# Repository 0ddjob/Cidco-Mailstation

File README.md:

# Cidco MailStation
The MailStation is a Z80 based device from the 20th Century used primarily for email using the POTS (PSTN dial up).<br>

It has a Z80??<br>

W.I.P.Z. ... ?<br>
(Will It Play Zork?)<br>

Apparently [YES!](https://www.fybertech.net/mailstation/images.php)<br>

Unfortunately it seems there is not much active interest or development on the MailStation ... ?<br>

## Videos
- [Cidco MailStation: Part 1 (Quick Look)](https://youtu.be/7wJat_JoTqo)

## [Memory Remapping](/Memory_Remap/)
Thanks to FyberOptic's work detailed [here](https://www.fybertech.net/mailstation/), I have reproduced his schematic and designed this small board to reorganise the memory map of the MailStation so that it might run CP/M.<br>

### Status
10-Jul-2025: Design still a work-in-progress<br>

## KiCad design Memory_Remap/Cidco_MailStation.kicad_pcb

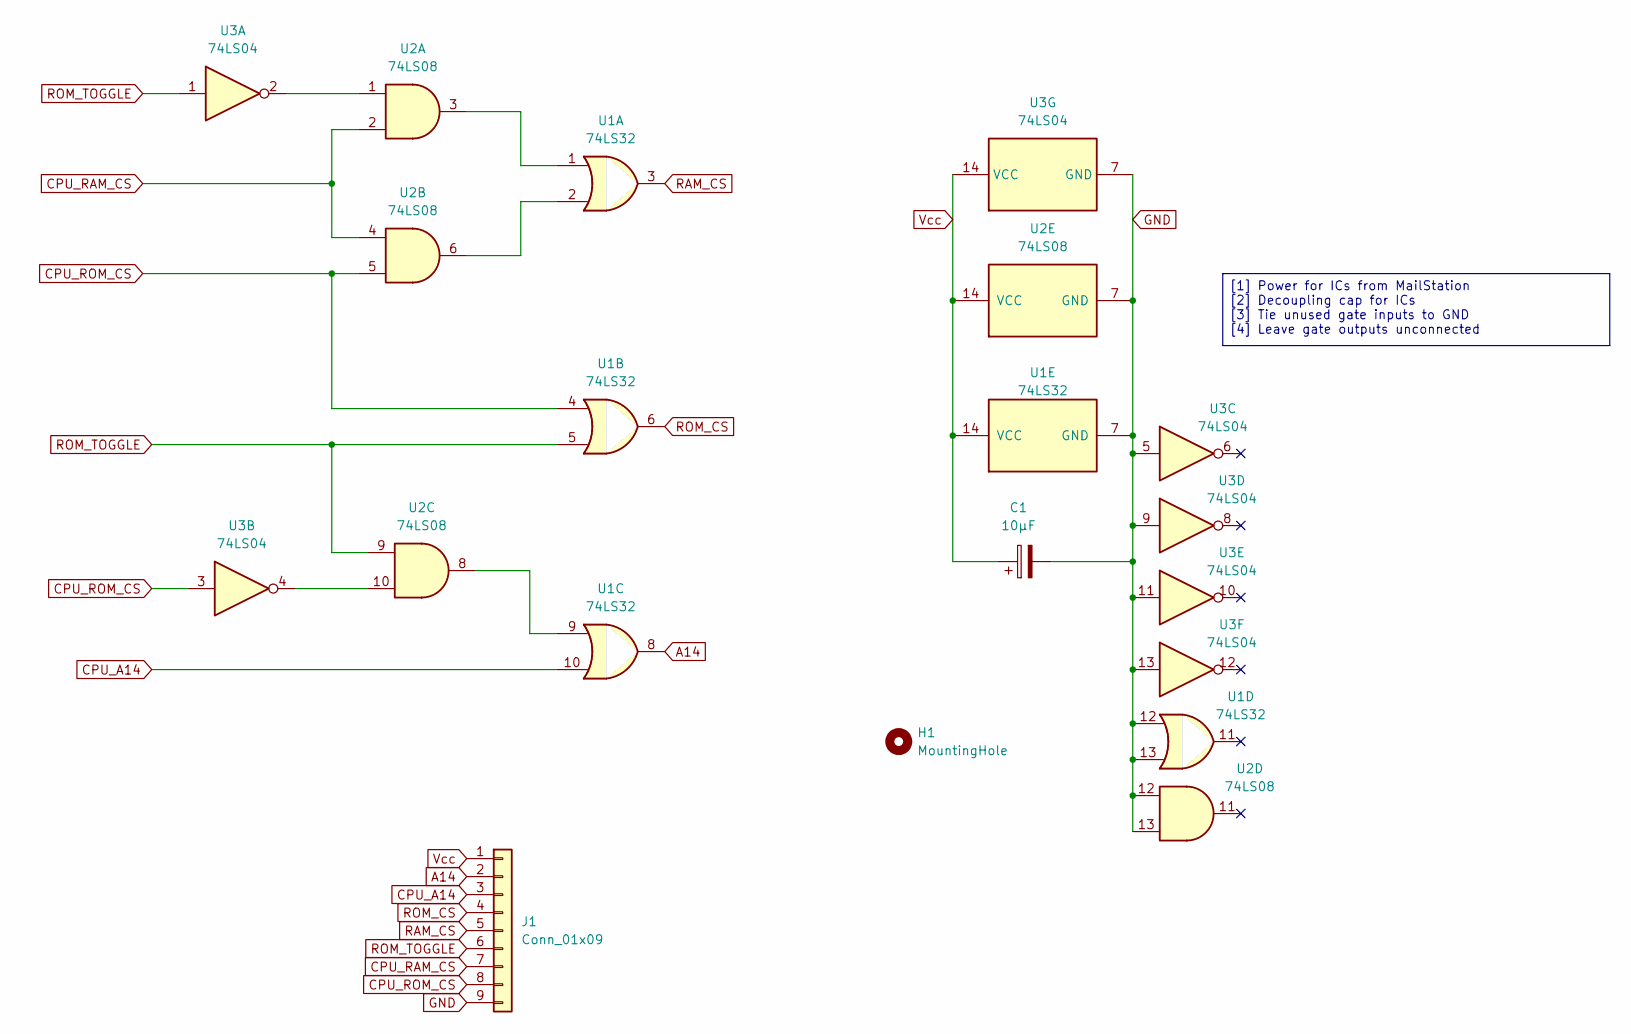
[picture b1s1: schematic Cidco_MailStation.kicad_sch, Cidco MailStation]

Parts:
C1: 10µF; CP_Radial_D5.0mm_P2.50mm
H1: MountingHole; MountingHole_3.2mm_M3
J1: Conn_01x09; PinHeader_1x09_P2.54mm_Vertical
U1: 74LS32; DIP-14_W7.62mm
U2: 74LS08; DIP-14_W7.62mm
U3: 74LS04; DIP-14_W7.62mm

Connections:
A14: J1.2, U1.8
CPU_A14: J1.3, U1.10
CPU_RAM_CS: J1.7, U2.2, U2.4
CPU_ROM_CS: J1.8, U1.4, U2.5, U3.3
GND: C1.2, J1.9, U1.7 (GND), U1.12, U1.13, U2.7 (GND), U2.12, U2.13, U3.5, U3.7 (GND), U3.9, U3.11, U3.13
unnamed: U1.1, U2.3
unnamed: U1.2, U2.6
unnamed: U1.9, U2.8
unnamed: U2.1, U3.2
unnamed: U2.10, U3.4
RAM_CS: J1.5, U1.3
ROM_CS: J1.4, U1.6
ROM_TOGGLE: J1.6, U1.5, U2.9, U3.1
Vcc: C1.1, J1.1, U1.14 (VCC), U2.14 (VCC), U3.14 (VCC)

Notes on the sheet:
[1] Power for ICs from MailStation [2] Decoupling cap for ICs [3] Tie unused gate inputs to GND [4] Leave gate outputs unconnected

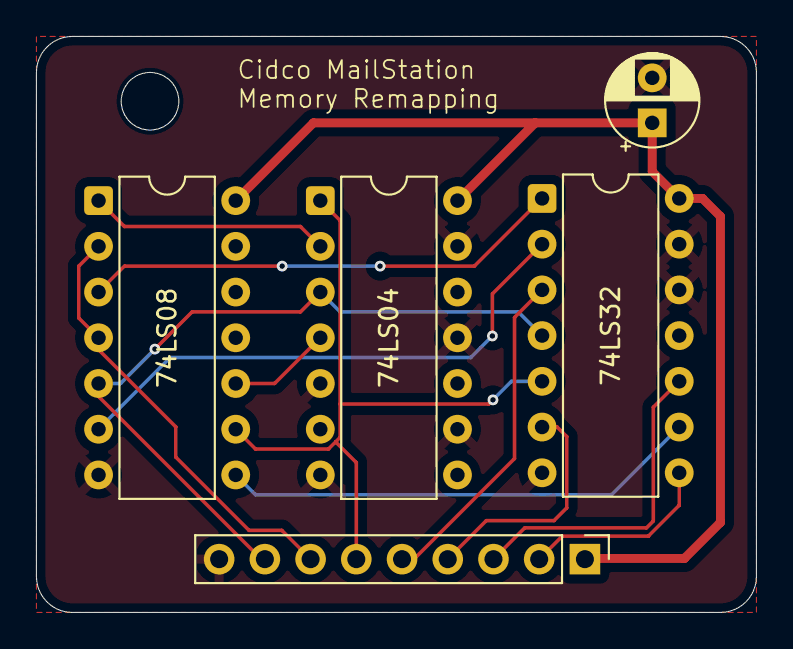
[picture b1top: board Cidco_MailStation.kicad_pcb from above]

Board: 2 copper layers, 40.0 x 32.0 mm, 6 parts (0 on the bottom side), 14 nets.
